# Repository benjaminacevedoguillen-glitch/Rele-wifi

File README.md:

# Placa Relay-WiFi

Placa de control con dos relés y conectividad WiFi para encender y apagar cargas de 220 V de forma remota. Es una alternativa económica de domótica para iluminación y pequeños electrodomésticos.

Proyecto de la materia **Montajes de Proyectos Electrónicos** (2.º cuatrimestre 2026).
Escuela de Educación Secundaria Técnica N° 5 "2 de Abril" – Temperley, Buenos Aires.

## Características

- 2 relés de 5 V con contactos NA, común y NC.
- Microcontrolador ESP32-C3 Super Mini con WiFi.
- Etapa de potencia aislada con optoacopladores.
- 2 entradas para sensores de proximidad (radar de aproximadamente 7 m).
- Conector UART reservado para ampliaciones.
- Alimentación de 12 V con regulador a 5 V.
- Diseñada en KiCad.

## Aplicaciones

- Iluminación de interiores y exteriores con encendido y apagado remoto.
- Iluminación programada por rango horario.
- Encendido automático por sensor de proximidad.
- Encendido remoto de electrodomésticos.

## Estructura del repositorio

- `Hardware/`: proyecto de KiCad, esquemático y PCB.
- `Software/`: firmware del ESP32-C3.

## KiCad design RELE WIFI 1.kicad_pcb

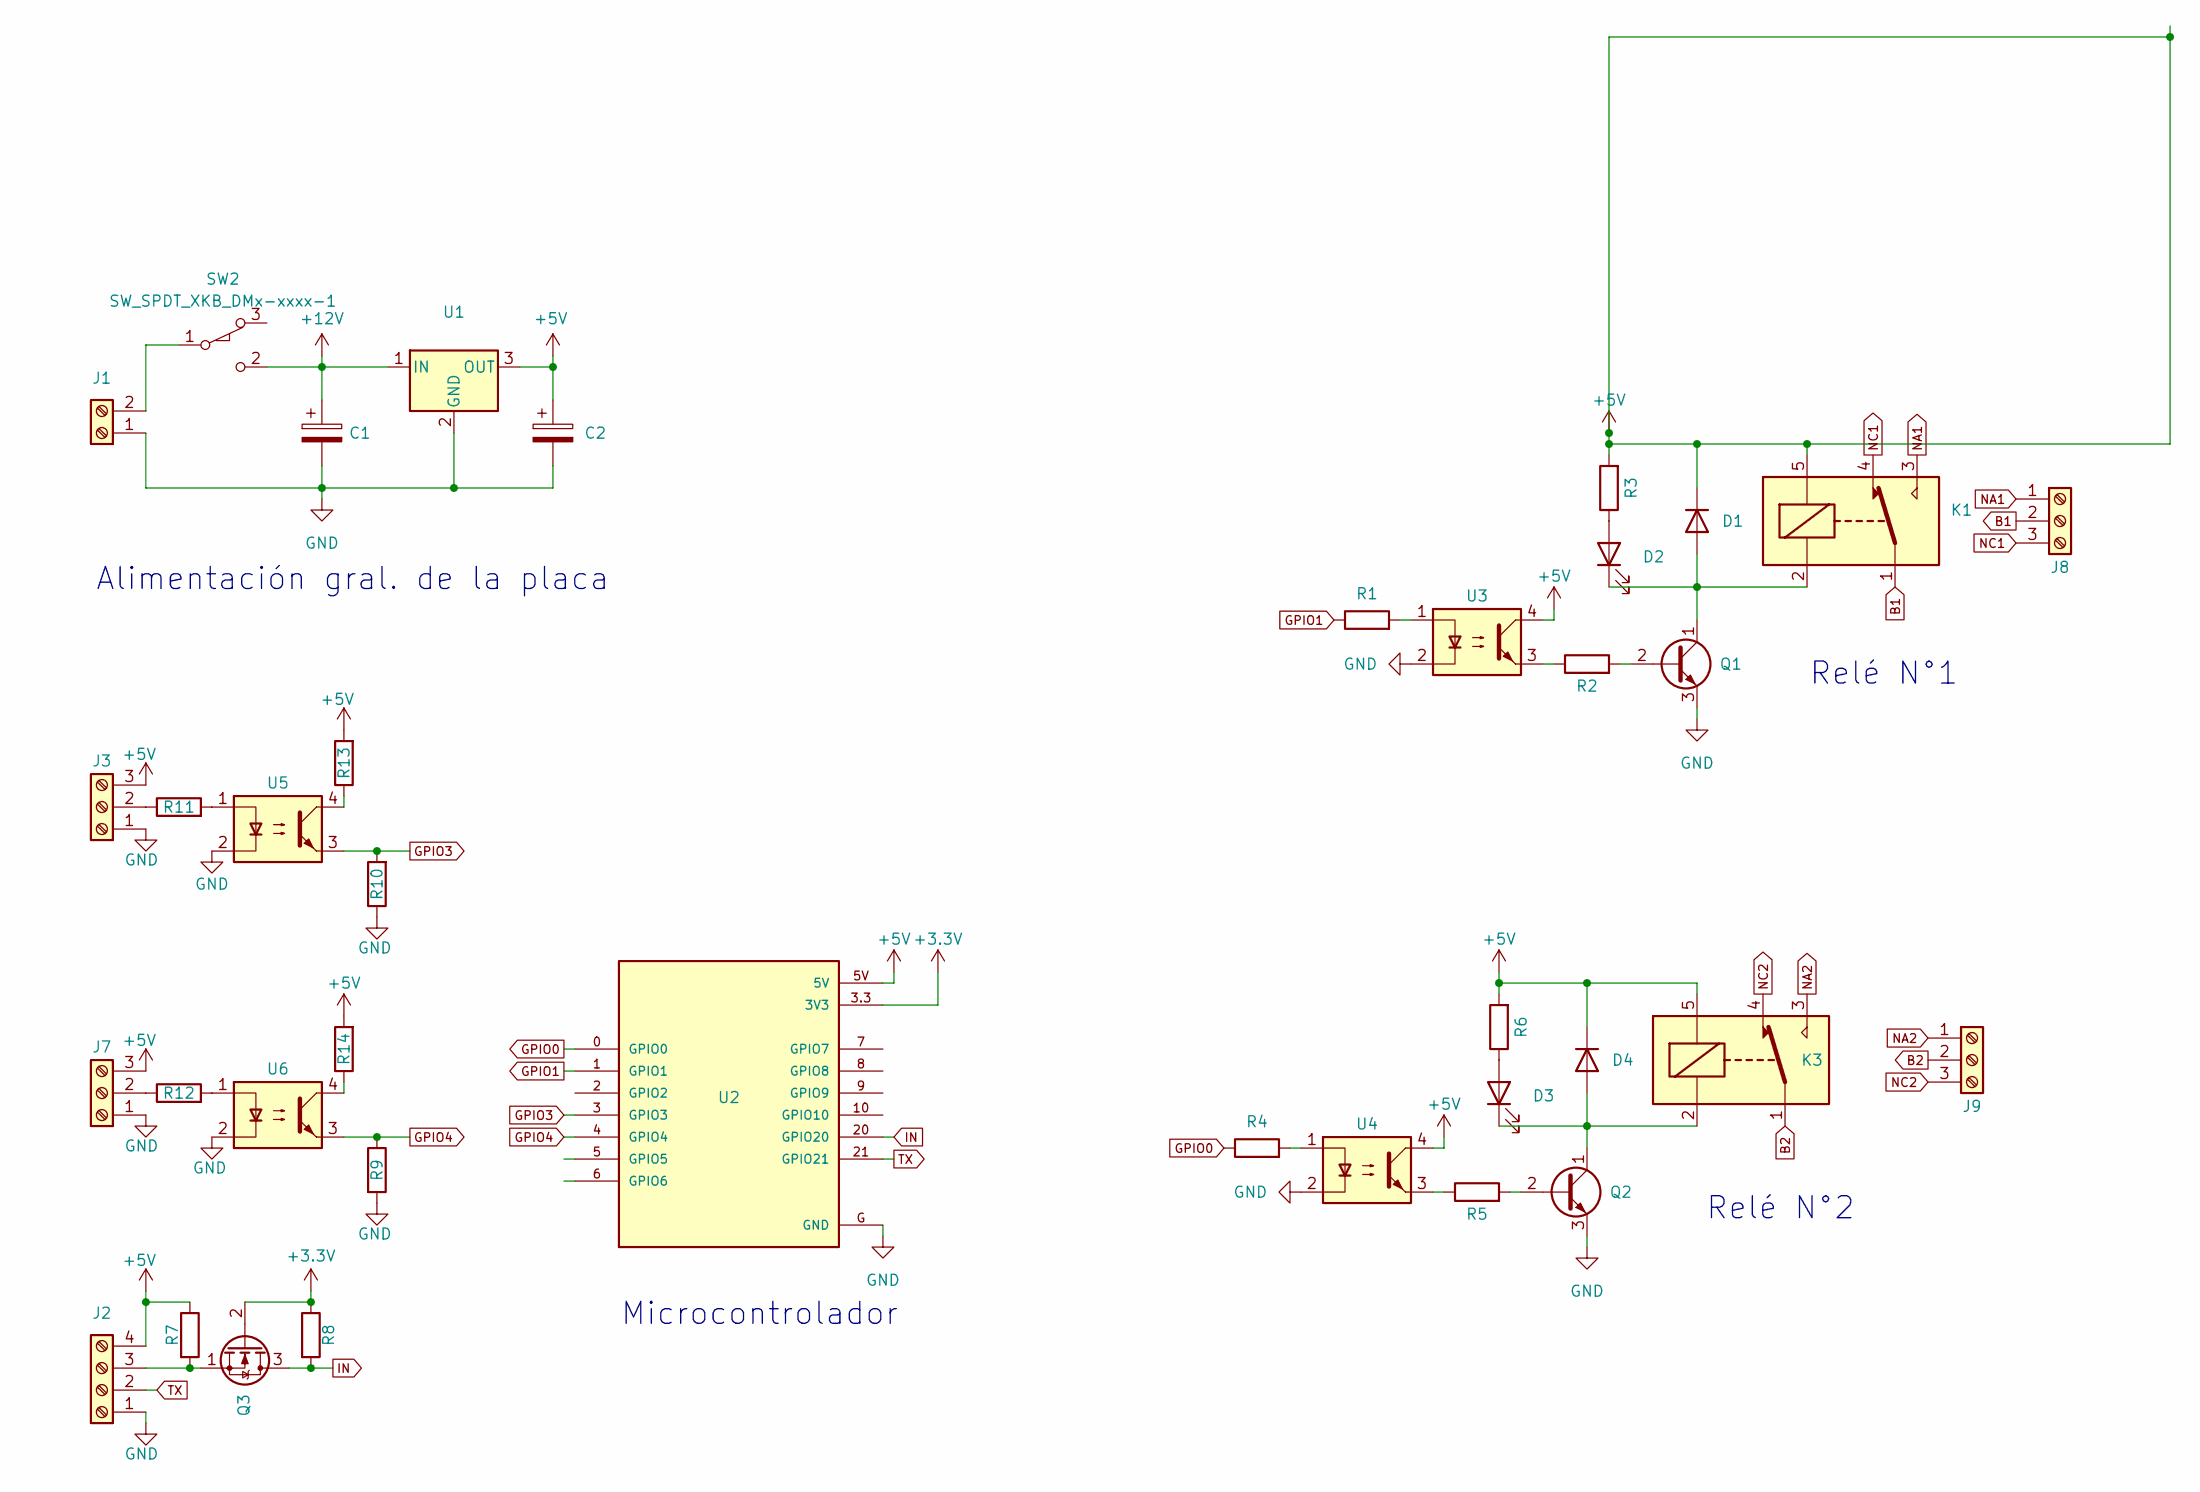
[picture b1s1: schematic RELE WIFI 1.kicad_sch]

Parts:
C1, C2: C_Polarized; C_Radial_D6.3mm_H5.0mm_P2.50mm
D1, D4: 1N4149; D_DO-35_SOD27_P7.62mm_Horizontal
D2, D3: LED; LED_D5.0mm
J1: Screw_Terminal_01x02; TerminalBlock_MaiXu_MX126-5.0-02P_1x02_P5.00mm
J2: Screw_Terminal_01x04; TerminalBlock_MaiXu_MX126-5.0-04P_1x04_P5.00mm
J3, J7, J8, J9: Screw_Terminal_01x03; TerminalBlock_MaiXu_MX126-5.0-03P_1x03_P5.00mm
K1, K3: SANYOU_SRD_Form_C; Relay_SPDT_SANYOU_SRD_Series_Form_C
Q1, Q2: BC547; TO-92_Inline
Q3: 2N7000; TO-92_Inline
R1, R2, R3, R4, R5, R7, R8, R9, R10, R11, R12, R13, R14: R; R_Axial_DIN0207_L6.3mm_D2.5mm_P7.62mm_Horizontal
R6: 1k; R_Axial_DIN0207_L6.3mm_D2.5mm_P7.62mm_Horizontal
SW2: SW_SPDT_XKB_DMx-xxxx-1; TerminalBlock_MaiXu_MX126-5.0-03P_1x03_P5.00mm
U1: L7805; TO-220-3_Vertical
U2: ESP32-C3_SUPERMINI_TH; MODULE_ESP32-C3_SUPERMINI_TH
U3, U4, U5, U6: PC817; DIP-4_W7.62mm_Socket_LongPads

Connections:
+3.3V: Q3.2 (G), R8.1, U2.3.3 (3V3)
+5V: C2.1, D1.1 (K), D4.1 (K), J2.4, J3.3, J7.3, K1.5, K3.5, R3.2, R6.2, R7.1, R13.2, R14.2, U1.3 (OUT), U2.5V, U3.4, U4.4
+12V: C1.1, SW2.2 (B), U1.1 (IN)
B1: J8.2, K1.1
B2: J9.2, K3.1
GND: C1.2, C2.2, J1.1, J2.1, J3.1, J7.1, Q1.3 (E), Q2.3 (E), R9.2, R10.1, U1.2 (GND), U2.G (GND), U3.2, U4.2, U5.2, U6.2
GPIO0: R4.1, U2.0 (GPIO0)
GPIO1: R1.1, U2.1 (GPIO1)
GPIO3: R10.2, U2.3 (GPIO3), U5.3
GPIO4: R9.1, U2.4 (GPIO4), U6.3
IN: Q3.3 (D), R8.2, U2.20 (GPIO20)
NA1: J8.1, K1.3
NA2: J9.1, K3.3
NC1: J8.3, K1.4
NC2: J9.3, K3.4
unnamed: D1.2 (A), D2.1 (K), K1.2, Q1.1 (C)
unnamed: D2.2 (A), R3.1
unnamed: D3.2 (A), R6.1
unnamed: D3.1 (K), D4.2 (A), K3.2, Q2.1 (C)
unnamed: J1.2, SW2.1 (A)
unnamed: J2.3, Q3.1 (S), R7.2
unnamed: J3.2, R11.1
unnamed: J7.2, R12.1
unnamed: Q1.2 (B), R2.2
unnamed: Q2.2 (B), R5.2
unnamed: R1.2, U3.1
unnamed: R2.1, U3.3
unnamed: R4.2, U4.1
unnamed: R5.1, U4.3
unnamed: R11.2, U5.1
unnamed: R12.2, U6.1
unnamed: R13.1, U5.4
unnamed: R14.1, U6.4
TX: J2.2, U2.21 (GPIO21)

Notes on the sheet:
Relé N°2
Alimentación gral. de la placa
Relé N°1
Microcontrolador

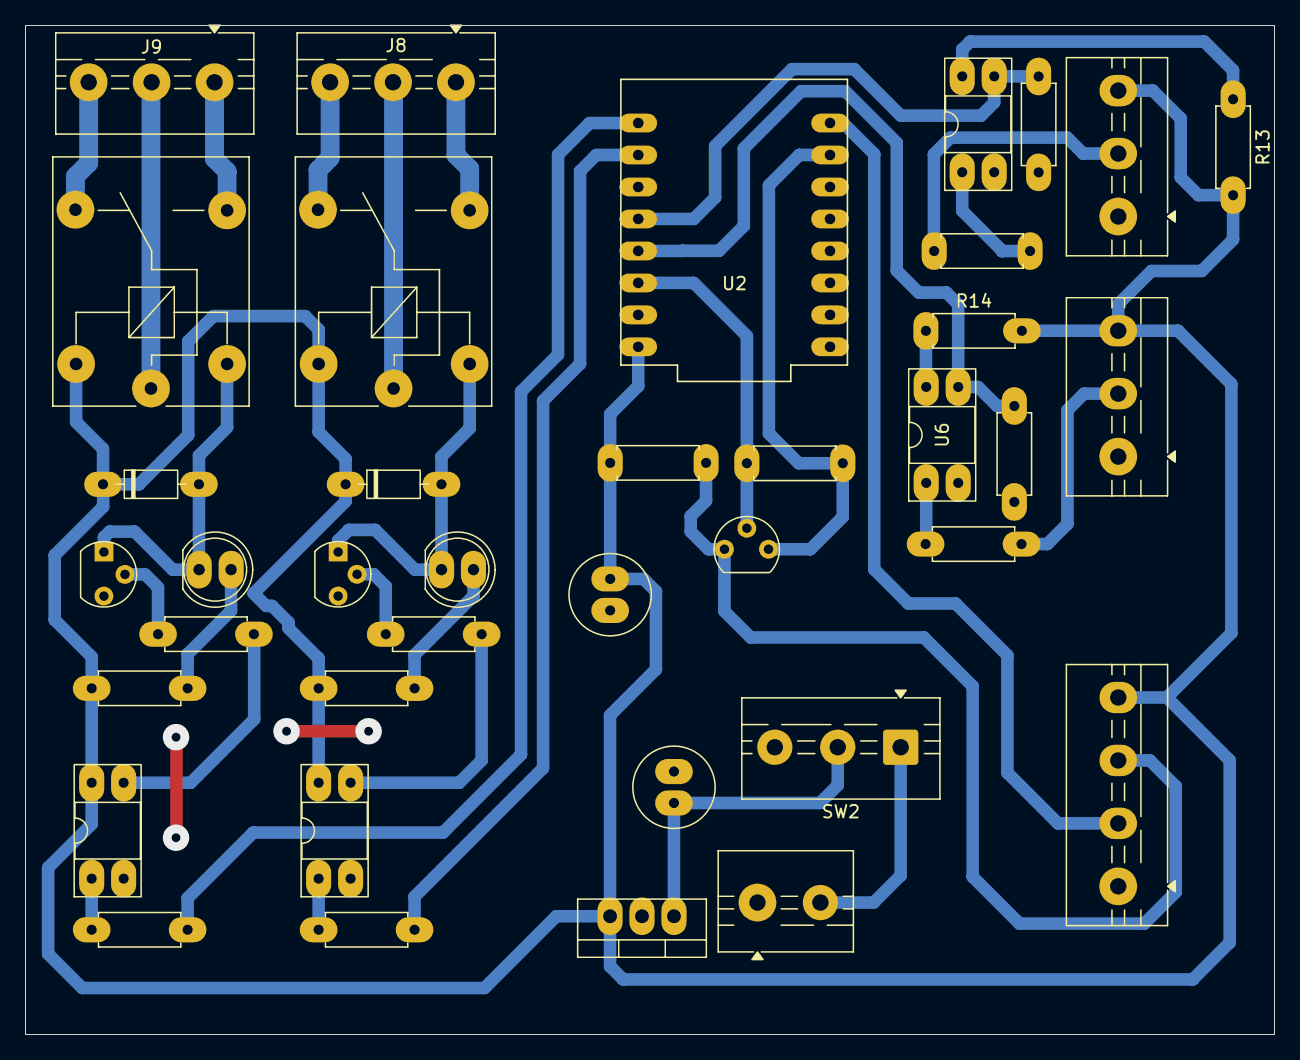
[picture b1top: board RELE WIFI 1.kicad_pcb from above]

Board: 2 copper layers, 99.2 x 80.2 mm, 38 parts (0 on the bottom side), 34 nets.
